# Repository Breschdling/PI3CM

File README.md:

# PI3CM
Raspberry 3 Carrier Board

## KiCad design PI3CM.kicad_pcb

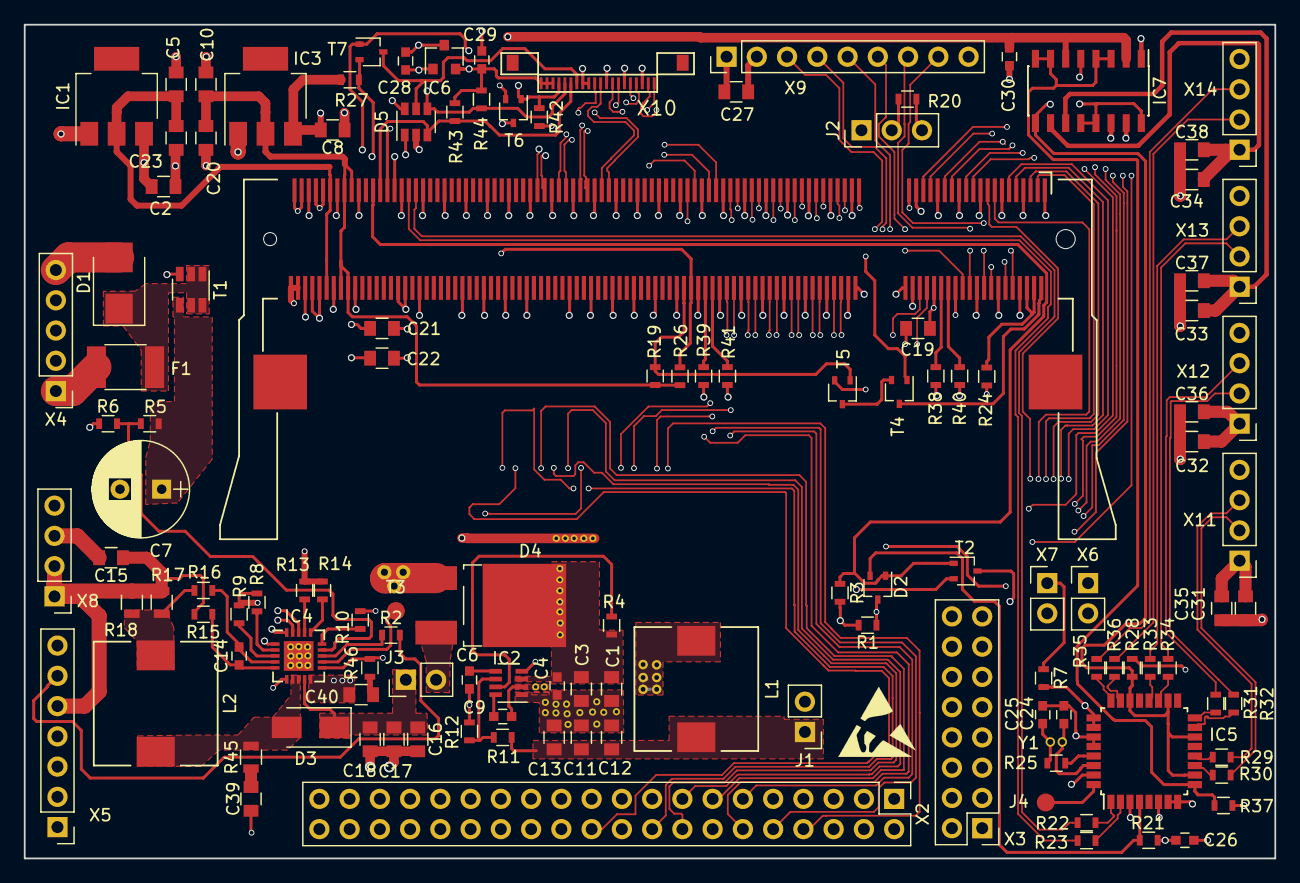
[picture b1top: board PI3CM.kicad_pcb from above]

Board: 4 copper layers, 105.0 x 70.0 mm, 127 parts (0 on the bottom side), 143 nets.

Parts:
C1, C3, C5, C10, C27: 10uF; C_0805
C2, C8, C19, C23, C40: 2.2uF; C_0805
C4, C9, C26, C28, C29, C30: 100nF; C_0603
C6, C14: 10nF; C_0603
C7: 220uF/16V; CP_Radial_D8.0mm_P3.50mm
C11, C12, C13, C15, C16, C17, C18, C20, C21, C22, C31, C32, C33, C34, C35, C36, C37, C38: 22uF; C_0805
C24, C25: 33pF; C_0603
C39: 4n7; C_0805
D1: SMBJ5.0CA; D_SMB_Standard
D2: BAT54C; SOT-323_SC-70
D3: SBR3U20SA; D_SMA_Standard
D4: RB095BM-30; TO-252-2Lead
D5: 82402305; SOT-23-6
F1: MF-MSMF250/16X; L_1812
IC1: AP7361C-25ER; SOT-223
IC2: TPS563219A; SOT-23-8
IC3: AP7361C-18ER; SOT-223
IC4: ACT2813; QFN-20-1EP_4x4mm_Pitch0.5mm
IC5: TUSB2046B; LQFP-32_7x7mm_Pitch0.8mm
IC6: AP2331; SOT-23
IC7: TPS2044B; SOIC-16_3.9x9.9mm_Pitch1.27mm
J1, J3: PH2x1_2.54; Pin_Header_Straight_1x02_Pitch2.54mm
J2: PH3x1_2.54; Pin_Header_Straight_1x03_Pitch2.54mm
J4: TEST_1P; Measurement_Point_Round-SMD-Pad_Small
L1, L2: 2.2uH; Choke_SMD_10.1x10.1_H6.5
R1, R3, R4, R5, R9, R19, R21, R26, R27, R28, R38, R39, R40, R41, R42: 100k; R_0603
R2: 100R; R_0603
R6, R8: 30k; R_0603
R7: 470R; R_0603
R10, R12, R20: 10k; R_0603
R11: 33k2; R_0603
R13, R14: 68k; R_0603
R15, R16, R24: 0R; R_0603
R17, R18: 50mR; R_0805
R22, R23, R29, R30, R31, R32, R33, R34, R35, R36: 22R; R_0603
R25, R37, R43, R44: 1k5; R_0603
R45: 0R47; R_0805
R46: 2R7; R_0603
T1: Si3421DV; TSOT-23-6_MK06A
T2, T4, T5, T6, T7: 2N7002; SOT-323_SC-70
T3: Test; Measurement_Point_Round-SMD-Pad_Small
X1: DDR2_SODIMM; Conn_TE-DDR2-SODIMM-0.6-200P
X2: PH20x2_2.54 female; Pin_Header_Straight_2x20_Pitch2.54mm
X3: CONN_02X08; Pin_Header_Straight_2x08_Pitch2.54mm
X4: PH5x1_2.54; Pin_Header_Straight_1x05_Pitch2.54mm
X5: PH7x1_2.54; Pin_Header_Straight_1x07_Pitch2.54mm
X6, X7: PH2x1_2.54; Pin_Header_Straight_1x02_Pitch2.54mm
X8, X11, X12, X13, X14: PH4x1_2.54; Pin_Header_Straight_1x04_Pitch2.54mm
X9: PH9x1_2.54 female; Socket_Strip_Straight_1x09_Pitch2.54mm
X10: XF2L-2035-1A
Y1: 6MHz; Crystal_Round_d3.1mm_Vertical

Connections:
+1V8: C10.1, C20.1, IC3.2, R19.2, R26.1, X1.183, X1.184, X1.185, X1.186
+2V5: C5.1, C23.1, IC1.2, X1.189, X1.190
+3V3: C2.2, C8.2, C19.2, C21.1, C26.2, C27.1, IC1.3, IC3.3, IC5.3, IC5.6, IC5.25, IC5.26, J1.2, J2.1, R1.2, R3.2, R7.2, R21.1, R24.2, R27.1, R28.2, X1.39, X1.40, X1.41, X1.42, X1.191, X1.192, X1.193, X1.194, X2.1, X2.17, X3.1, X9.1
+5V: C1.1, C3.1, C4.2, C22.1, C28.2, C30.2, D4.2, IC2.3, IC6.3, IC7.2, IC7.6, R4.2, X1.197, X1.198, X1.199, X1.200, X2.2, X2.4
+5VP: C29.2, D5.1, IC6.2, R43.1, R44.1, T7.1, X10.18, X10.19, X10.20
/Power/BAT: C15.1, R15.1, R17.1, R18.1, X5.5, X8.1, X8.2
/Power/Buck3V3: C11.1, C12.1, C13.1, J1.1, L1.2, R11.2
/Power/EMMC_DISABLE_N: T4.3, X1.2
/Power/EMMC_EN_N_1V8: R19.1, T5.1, X1.90
/Power/EN: IC2.7, R4.1
/Power/HZ: IC4.14, R5.1, R6.2
/Power/LED1: IC4.1, X5.1
/Power/LED2: IC4.20, X5.2
/Power/LED3: IC4.19, X5.3
/Power/LED4: IC4.18, X5.4
/Power/PB: IC4.13, R2.1
/Power/PG: D2.3, IC2.4, R1.1, X6.1
/Power/RUN: D2.1, R3.1, T2.1, X1.177
/Power/VFB: IC2.6, R11.1, R12.2
/Power/VIN: C7.1, C40.2, D4.1, IC4.10, R5.2, T1.4
/Power/VOUT: C16.1, C17.1, C18.1, D3.1, IC4.9, J3.1
/Power/Vbat: D4.3, J3.2
/gpio/GPIO0: X1.3, X2.27
/gpio/GPIO1: X1.5, X2.28
/gpio/GPIO2: X1.9, X2.3
/gpio/GPIO3: X1.11, X2.5
/gpio/GPIO4: X1.15, X2.7
/gpio/GPIO5: X1.17, X2.29
/gpio/GPIO6: X1.21, X2.31
/gpio/GPIO7: X1.23, X2.26
/gpio/GPIO8: X1.27, X2.24
/gpio/GPIO9: X1.29, X2.21
/gpio/GPIO10: X1.33, X2.19
/gpio/GPIO11: X1.35, X2.23
/gpio/GPIO12: X1.45, X2.32
/gpio/GPIO13: X1.47, X2.33
/gpio/GPIO14: X1.51, X2.8
/gpio/GPIO15: X1.53, X2.10
/gpio/GPIO16: X1.57, X2.36
/gpio/GPIO17: X1.59, X2.11
/gpio/GPIO18: X1.63, X2.12
/gpio/GPIO19: X1.65, X2.35
/gpio/GPIO20: X1.69, X2.38
/gpio/GPIO21: X1.71, X2.40
/gpio/GPIO22: X1.75, X2.15
/gpio/GPIO23: X1.77, X2.16
/gpio/GPIO24: X1.81, X2.18
/gpio/GPIO25: X1.83, X2.22
/gpio/GPIO26: X1.87, X2.37
/gpio/GPIO27: X1.89, X2.13
/gpio/GPIO30: X1.34, X3.3
/gpio/GPIO31: X1.36, X3.4
/gpio/GPIO32: X1.46, X3.5
/gpio/GPIO33: X1.48, X3.6
/gpio/GPIO34: X1.52, X3.7
/gpio/GPIO35: X1.54, X3.8
/gpio/GPIO36: X1.58, X3.9
/gpio/GPIO37: X1.60, X3.10
/gpio/GPIO38: X1.64, X3.11
/gpio/GPIO39: X1.66, X3.12
/gpio/GPIO40: X1.70, X3.13
/gpio/GPIO41: X1.72, X3.14
/gpio/GPIO42: X1.76, X3.15
/gpio/GPIO43: X1.78, X3.16
/io/CEC: D5.5, T7.3, X10.14
/io/D0R_N: IC5.2, R23.1
/io/D0R_P: IC5.1, R22.1
/io/D0_N: R23.2, X1.167
/io/D0_P: R22.2, X1.165
/io/D1R_N: IC5.11, R30.2
/io/D1R_P: IC5.12, R29.2
/io/D1_N: R30.1, X11.2
/io/D1_P: R29.1, X11.3
/io/D2R_N: IC5.15, R32.2
/io/D2R_P: IC5.16, R31.2
/io/D2_N: R32.1, X12.2
/io/D2_P: R31.1, X12.3
/io/D3R_N: IC5.19, R34.2
/io/D3R_P: IC5.20, R33.2
/io/D3_N: R34.1, X13.2
/io/D3_P: R33.1, X13.3
/io/D4R_N: IC5.23, R36.2
/io/D4R_P: IC5.24, R35.2
/io/D4_N: R36.1, X14.2
/io/D4_P: R35.1, X14.3
/io/HDMI_CEC: R27.2, T7.2, X1.171
/io/HDMI_CLK_N: X1.111, X10.11
/io/HDMI_CLK_P: X1.113, X10.10
/io/HDMI_D0_N: X1.117, X10.8
/io/HDMI_D0_P: X1.119, X10.7
/io/HDMI_D1_N: X1.123, X10.5
/io/HDMI_D1_P: X1.125, X10.4
/io/HDMI_D2_N: X1.129, X10.2
/io/HDMI_D2_P: X1.131, X10.1
/io/HDMI_HPD: D5.6, R42.1, T6.1, X10.17
/io/HDMI_HPD_N_1V8: R26.2, T6.3, X1.88
/io/HDMI_SCL: D5.3, R43.2, X1.175, X10.15
/io/HDMI_SDA: D5.4, R44.2, X1.173, X10.16
/io/OVRCUR: IC5.10, IC5.14, IC5.18, IC5.22, IC7.9, IC7.12, IC7.13, IC7.16, R28.1
/io/PWRON: IC5.9, IC7.3, IC7.4, IC7.7, IC7.8, R37.1
/io/SDX_CLK: X1.10, X9.5
/io/SDX_CMD: X1.12, X9.4
/io/SDX_D0: X1.16, X9.3
/io/SDX_D1: X1.18, X9.8
/io/SDX_D2: X1.22, X9.7
/io/SDX_D3: X1.24, X9.6
/io/Vbus1: C31.2, C35.2, IC7.15, X11.1
/io/Vbus2: C32.2, C36.2, IC7.14, X12.1
/io/Vbus3: C33.2, C37.2, IC7.11, X13.1
/io/Vbus4: C34.2, C38.2, IC7.10, X14.1
GND: C1.2, C2.1, C3.2, C4.1, C5.2, C6.2, C7.2, C8.1, C10.2, C11.2, C12.2, C13.2, C15.2, C16.2, C17.2, C18.2, C19.1, C20.2, C21.2, C22.2, C23.2, C24.2, C25.2, C26.1, C27.2, C28.1, C29.1, C30.1, C31.1, C32.1, C33.1, C34.1, C35.1, C36.1, C37.1, C38.1, C39.1, D1.2, D5.2, IC1.1, IC2.1, IC3.1, IC4.6, IC4.11, IC4.21, IC5.7, IC5.8, IC5.27, IC5.28, IC5.31, IC6.1, IC7.1, IC7.5, J2.3, R6.1, R8.2, R9.2, R10.2, R12.1, R13.1, R14.1, R20.1, R37.2, R38.2, R39.2, R40.2, R41.2, R42.2, R46.1, T1.3, T2.2, T5.2, T6.2, X1.1, X1.7, X1.8, X1.13, X1.14, X1.19, X1.20, X1.25, X1.26, X1.31, X1.32, X1.37, X1.38, X1.43, X1.44, X1.49, X1.50, X1.55, X1.56, X1.61, X1.62, X1.67, X1.68, X1.73, X1.74, X1.79, X1.80, X1.85, X1.86, X1.91, X1.92, X1.97, X1.98, X1.103, X1.104, X1.109, X1.110, X1.115, X1.116, X1.121, X1.122, X1.127, X1.133, X1.134, X1.139, X1.140, X1.145, X1.146, X1.151, X1.152, X1.157, X1.163, X1.164, X1.168, X1.169, X1.170, X1.181, X1.182, X1.187, X1.188, X1.195, X1.196, X2.6, X2.9, X2.14, X2.20, X2.25, X2.30, X2.34, X2.39, X3.2, X4.5, X5.7, X6.2, X8.3, X8.4, X9.2, X10.3, X10.6, X10.9, X10.12, X10.13, X11.4, X12.4, X13.4, X14.4
unnamed: C6.1, IC2.5
unnamed: C9.1, IC2.2, L1.1
unnamed: C9.2, IC2.8
unnamed: C14.1, IC4.5, R15.2
unnamed: C14.2, IC4.4, R16.2
unnamed: C24.1, IC5.30, Y1.1
unnamed: C25.1, R25.1, Y1.2
unnamed: C39.2, R45.1
unnamed: C40.1, R46.2
unnamed: D1.1, F1.1, T1.1, T1.2, T1.5, T1.6
unnamed: D3.2, IC4.7, IC4.8, L2.1, R45.2
unnamed: F1.2, X4.1
unnamed: IC4.2, R8.1
unnamed: IC4.3, R9.1
unnamed: IC4.12, T3.1
unnamed: IC4.15, R10.1
unnamed: IC4.16, R14.2
unnamed: IC4.17, R13.2
unnamed: IC5.29, R25.2
unnamed: IC5.32, J4.1
unnamed: J2.2, R20.2, T4.1
unnamed: L2.2, R16.1, R17.2, R18.2
unnamed: R2.2, X5.6
unnamed: R7.1, X7.1
unnamed: R24.1, X1.4, X1.6
unnamed: R38.1, X1.30
unnamed: R39.1, X1.84
unnamed: R40.1, X1.28
unnamed: R41.1, X1.82
unnamed: T2.3, X7.2
unnamed: T4.2, T5.3
nRESET: D2.2, IC5.4, R21.2

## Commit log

2021-03-07 Add Schematic PDF
2021-03-07 Create LICENSE
